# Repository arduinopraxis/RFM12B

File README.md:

# RFM12B
RFM12B Wireless Applications

Boards and Code for Wireless Applications with RFM12B Transceiver

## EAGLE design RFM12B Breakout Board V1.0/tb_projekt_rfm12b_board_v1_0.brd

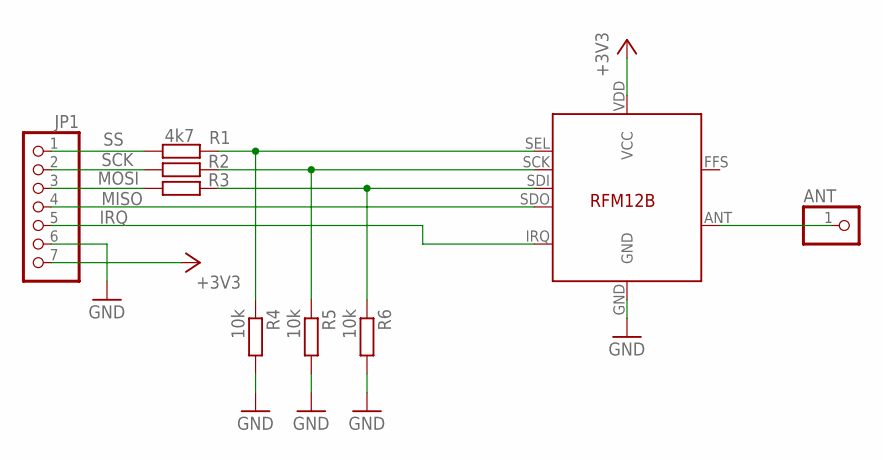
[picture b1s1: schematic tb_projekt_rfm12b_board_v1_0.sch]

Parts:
ANT: PINHD-1X1; 1X01
IC1: RFM12B
JP1: PINHD-1X7; 1X07
R1: 4k7; 0207/7
R2, R3: R-EU_0207/7; 0207/7
R4, R5, R6: 10k; 0207/7

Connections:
+3V3: IC1.VDD (VCC), JP1.7
GND: IC1.GND, JP1.6, R4.2, R5.2, R6.2
IRQ: IC1.IRQ, JP1.5
MISO: IC1.SDO, JP1.4
MOSI: JP1.3, R3.2
unnamed: ANT.1, IC1.ANT
unnamed: IC1.SDI, R3.1, R6.1
unnamed: IC1.SCK, R2.1, R5.1
unnamed: IC1.SEL, R1.2, R4.1
SCK: JP1.2, R2.2
SS: JP1.1, R1.1

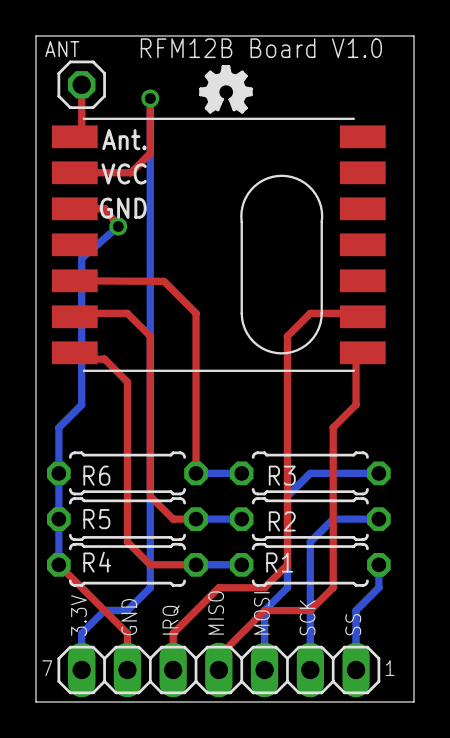
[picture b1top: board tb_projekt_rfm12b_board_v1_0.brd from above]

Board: 2 copper layers, 21.0 x 37.0 mm, 10 parts (0 on the bottom side), 11 nets.

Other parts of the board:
U$1: OSHW_FILLX100_NOTEXT
